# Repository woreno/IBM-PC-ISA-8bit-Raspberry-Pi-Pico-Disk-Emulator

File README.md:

# ISA-Raspberry-Pi-Pico-Disk-Emulator
A Raspberry Pi Pico **floppy disk and harddisk emulator** for older computers/operating systems that **relies only** on BIOS for disk accesses. Its a ISA-8 bit board. "It can let you use it your physical floppy drives or, floppy images on demand, using a tiny screen and a joystick". As this is a DIY electronics and software project, use this at your own risk.
Also the Raspberry Pi Pico C/PIO code is experimental - it just works fine with O0 (despite i attempted to set critical parts to no optimization, i didnt ran) - so this is an open issue, and i had to fine-tune the screen clocks using DEFINEs. 

**Included** 
  - Kicad ISA-8bit prototype schematic
    - this sketch has wide-traces because i use to transfer PCB designs using photo-paper + iron and etch them with ferric chloride (so this process sometimes fails with thin traces, so i use wider traces)  
  - C and ASM code
  - building scripts (windows only)
  - Amstrad PPC512/640 rear expansion DB37 and DB25 ports diagram 
      - this project was tested with an Amstrad PPC640 hence ribbon cables were used instead of a ISA-8bit edge.
  - Memory addressing and connection simple diagrams

**Project Description**

   This ISA-8bit board implements new INT13h and INT19h BIOS software interrupts handlers for disk access and bootstrapping at 0xC8000. Instead of a having the typical ROM, a Raspberry Pi Pico serves these addresses with its own memory. Theres a mini TFT (ST7735), a Joystick, and a SDCard adapter connected by flat ribbon cables that can be attached to a front-panel. The board supports a FAT16 file system containing directories, floppy disk images, and a raw harddisk image (it must be named "hdd.ima" at the root directory). Using the joystick is possible to enable the harddisk image use, navigate SDCard filesystem, and assign floppy disk images to A: and B: drives at any time; theres also the option to select the physical drive instead of floppy disks. The bootstrap code (int19h) is needed for older computers not supporting booting from hard disks so it will place INT13h passing the drive (0x80) and if the hdd.ima file exists, it will boot just as fine.
   The advantage of replacing INT13h or jumping to the factory INT13h, is that is possible to enable the use of the physical drive or using a floppy disk image on demand. However, only ancients Operating Systems uses INT13h directly, so everything that is Windows-386 enhanced mode and beyond - that uses drivers for talking directly with floppy drives and harddisk via IO ports - doesn't belong to this project. 

**Electronics side**
  * Uses 2 74LS244 for multiplexing the address lines A0:A11 to the Raspberry Pi Pico
  * Uses 1 74HC244 for multiplexing the SDCard and TFT lines. The code calls turn_SD() and turnDisplay()
    to activate these lines before placing calls
  * Uses 1 GAL Atmel ATF16v8B for decoding the address 0xC8000 using the A15:A19 lines, along the
    memory read and memory write signals (/MEMR, /MEMW)
  * It pulls down the signal IOREADY using a 2N3904 transistor so it can finish the memory access requests
  * Uses a 2-axis joystick which swings 2 lines between -5V to 5V according to the side (left/right, up/down); these
    lines are connected to 2 ADC channels on the Raspberry Pi Pico
  * Uses 1 74HCT04 for inverting ENABLE_SD and /ENABLE_LOW_ADDR signals for multiplexing some lines, using the 244 buffers
  * Uses some voltage dividers with resistors for 5V to 3.3V level conversion next to some Raspberry Pi Pico GPIO 
  * Uses a bidirectional bus converter TXS0108E, from/to 3.3V to 5V, for the databus interface, operated with a Output Enable Signal to block them from the main 8086 PC databus

**Software side - Raspberry Pi Pico - Core 0**
  * This CPU core is on loop waiting for data from one master PIO program (master_pio). This master_pio is waiting for memr_pio or memw_pio PIO programs for producing and IRQ0.  
  * These previous 2 PIO programs (they are equal, just differ on the line they use, MEMR or MEMW): the PIO program keeps waiting for these signals to be HIGH - they come HIGH from the ATF16v8b when the 0xC8XXX is on the address bus as well one of /MEMR or /MEMW are LOW; after, the PIO Program immediately puts the IOWAIT line to HIGH, and a transistor connected to it, will pull down the IOREADY line to indicate the 8086 that needs more time. After, the master PIO program transfers control to the C program which reads all the address lines (enabling and disabling /EN_ADDR_LOW); reads which MEMR/W line is HIGH accordantly reads or writes the local C-Array, as well controling the databus converter signal DB_ENABLE_OE. At the end, the IOWAIT is lowered, and in case of a writing, the databus is left active for more a period for settling.
  
**Software side - Raspberry Pi Pico - Core 1**
* This CPU core is always on a loop:
    1) pooling the shared area variable "START_OPERATION" flag
    2) pooling the joystick values
    3) updating the graphical interface in the TFT in case of joystick movement
* The INT13h code saves the registers to the shared-variable area, and writes the START_OPERATION flag, as soon this happen the code knowns how to handle INT13h by reading or writing the SDCard. The code extracts the Cylinder-Head-Sector from the CPU registers, converts to LBA and reads and writes accordantly the virtual disk images. The core code and INT13h code uses the shared-buffer for transfering the r/w data; the 8086 CPU or the Raspberry Core is put to rest before the shared-buffer is going to be wrote by one of them.

**Software side - Raspberry Pi Pico - Core 1 - FileSystem and SDCard**
  * The FAT file system access is done with my own  library. Once a floppy disk image is loaded by using the user interface (or hdd.ima is present) the file is checked for contiguityusing "fs_checkSequence" (that's it if the file clusters are sequential, this is basically true when files don't expand) - if is this is true, then the r/w disk access is done faster using "fs_rw_sequential_512B", as the contents are indexed as 512 bytes starting at the first cluster of the file.
  * The SDCard access is done with my own library - it reads/writes 512blocks - incomplete code alert: OLDER SD CARDS might not work. 

**Software side - Raspberry Pi Pico - Core 1 - User interface**
  * The ST7735 TFT screen library its my own. The initialization code was borrowed from https://github.com/afiskon/stm32-st7735/ . This screen seems to demand a RESET line, i don't use it and i connect both RESET and BACKLIGHT lines to a pullup. I found if the initialization code is sent at lower speed, later commands can run at faster speed without requiring a RESET signal several toogling at the initialization. This saved me a 1 GPIO.
  * My own draw library abstracts calls to the screen primitive functions (drawing pixels, rectangles) with preprocessor DEFINEs.
  * My own user-interface library have base and derived classes to create lists with options, also specifing a source class. These later are like adapter classes that enable to create lists from a source, like a text file or a filesystem, in example to render a menu to navigate the master-boot-records and filesystems within. 

**Software side - 8086 PC Option ROM aspects**
  * The 8086-PC BIOS scans the upper memory addresses for option ROMs. These ROMs must include at their first bytes 0xAA55 (2 bytes), the total in 512-bytes blocks(1 byte), and all their bytes shall sum to zero (8-bit sum).
  
**Software side - 8086 PC Option ROM**
  * The ROM in written in ASM and compiled in Turbo Assembler in a DOSBOX enviroment.
  * After the 8086 code is compiled and linked with TASM, a utility strips the MZ-header, sums all bytes and writes the remain to 0, and places this remain into the compiled code, in a reserved, 1-byte place. After, the utility resizes this image to accomodate the buffer, and shared-variables area, and converts it to a C hexadecimal array. This array is included into Raspberry Pi Pico C++ program and has some C identifiers pointing to it. This array is served as the beggining of 0xC8000: boot code, INT13h, INT19h handlers, a buffer reserved for transfering data used by INT13h, a shared-variables-area, and the DBTs (disk base table). The DBTs are BIOS structures are served when INT13h, function 8 (get params) and need to be dinamically changed accordantly the floppy disk image selected (ie, 720KB or 1440KB).
  * When the ROM boots it saves the factory Int13h pointer (sitting at address 4*0x13) into the shared-variables area above the far-jump opcode (0xEA); then replaces the factory pointer at that address with the new Int13h pointer located at 0xC8xxx.
  * On Int19h, the new handler code iterates the 3 drives (0,1,0x80) reading the first sector with Int13h to 0x7C00, checking for the boot flag 0xAA55 at bytes 510 and 511, if success, it jumps to 0x7C00.
  *  On  Int13h, the new handler code will save the registers to the shared-variables area also checking there, if the drive is selected as physical. If physical, it will restore the registers and jump to the far-jump opcode along the saved factory Int13h address (transfering control to the factory Int13h to handle the physical drive). Otherwise the new code it will set the flag START_OPERATION at the shared-variables area to start exchanging data with the Raspberry core, also both using CMD and CMDRES flags to put any of the cpus resting while the other is writting data on the shared-buffer. At the end, the registers likely changed by the C code (for instance for function 8 get params) are restored.

**Software side - ATF16v8b pins logical functions**
  * This code specifies as outputs the MEMR and MEMW pins, these two outputs go to the Raspbery Pi Pico; as inputs the A15:19 address bus lines, /MEMR, /MEMW bus signals. When the A15:19 is 11001, and /MEMR=0 or /MEMW=0 it activates as HIGH the MEMR or MEMW output pins, thus decoding the 0xC8XXX address on memory accesses.

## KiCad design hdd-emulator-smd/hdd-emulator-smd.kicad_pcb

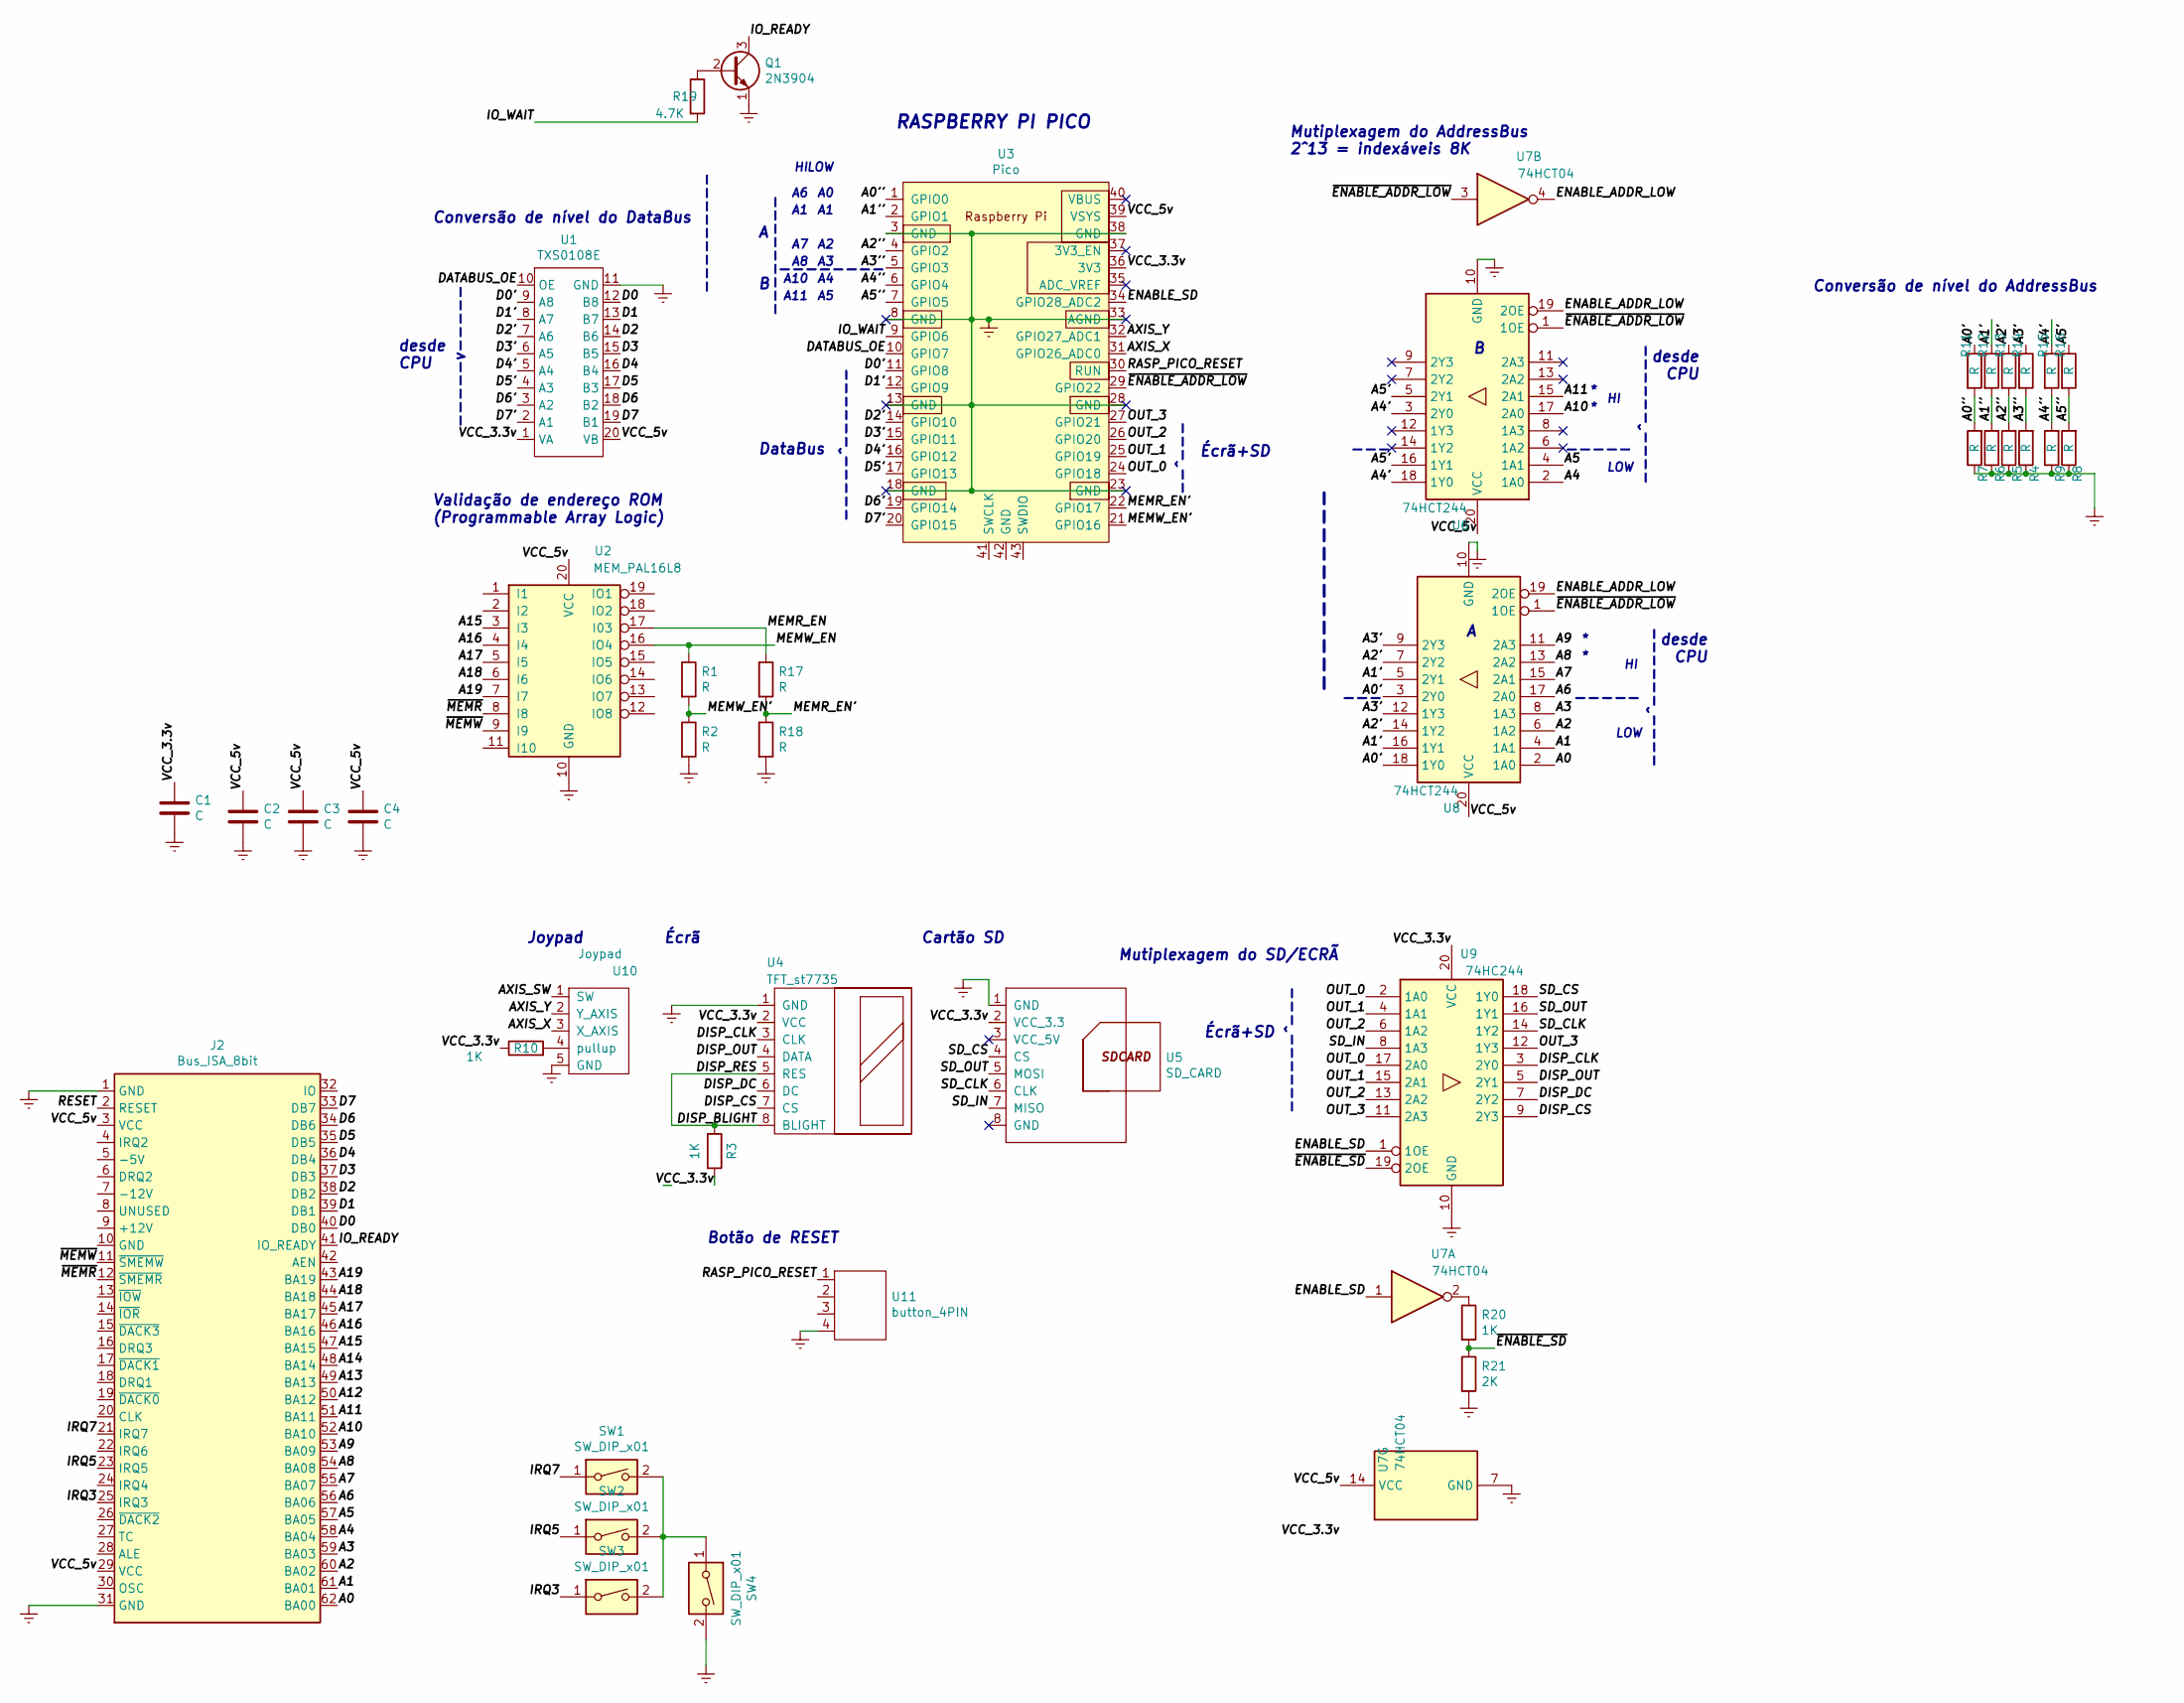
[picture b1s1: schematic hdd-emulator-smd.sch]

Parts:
C1, C2, C3, C4: C; standard_2pins_half
J2: Bus_ISA_8bit; ISA_8bit_edge
Q1: 2N3904; TO-92_Inline
R1, R2, R4, R5, R6, R7, R8, R9, R11, R12, R13, R14, R15, R16, R17, R18: R; R_0201_0603Metric
R3, R10, R20: 1K; R_0201_0603Metric
R19: 4.7K; R_0201_0603Metric
R21: 2K; R_0201_0603Metric
SW1, SW2, SW3, SW4: SW_DIP_x01; jumper_set_1
U1: TXS0108E; standard_DIP_10pins_doubleBody
U2: MEM_PAL16L8; standard_DIP_20pins_thin_body
U3: Pico; RPi_Pico_SMD_THT
U4: TFT_st7735; PinHeader_1x08_P2.54mm_Vertical
U5: SD_CARD; PinHeader_1x08_P2.54mm_Vertical
U6, U8: 74HCT244; standard_DIP_20pins_thin_body
U7: 74HCT04; standard_DIP_14OvalPins
U9: 74HC244; standard_DIP_20pins_thin_body
U10: Joypad; PinHeader_1x05_P2.54mm_Vertical
U11: button_4PIN; BUTTON_4PIN

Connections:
/A0: J2.62 (BA00), U8.2 (1A0)
/A0': R11.1, U8.3 (2Y0), U8.18 (1Y0)
/A0'': R7.2, R11.2, U3.1 (GPIO0)
/A1: J2.61 (BA01), U8.4 (1A1)
/A1': R12.1, U8.5 (2Y1), U8.16 (1Y1)
/A1'': R6.2, R12.2, U3.2 (GPIO1)
/A2: J2.60 (BA02), U8.6 (1A2)
/A2': R13.1, U8.7 (2Y2), U8.14 (1Y2)
/A2'': R5.2, R13.2, U3.4 (GPIO2)
/A3: J2.59 (BA03), U8.8 (1A3)
/A3': R14.1, U8.9 (2Y3), U8.12 (1Y3)
/A3'': R4.2, R14.2, U3.5 (GPIO3)
/A4: J2.58 (BA04), U6.2 (1A0)
/A4': R15.1, U6.3 (2Y0), U6.18 (1Y0)
/A4'': R9.2, R15.2, U3.6 (GPIO4)
/A5: J2.57 (BA05), U6.4 (1A1)
/A5': R16.1, U6.5 (2Y1), U6.16 (1Y1)
/A5'': R8.2, R16.2, U3.7 (GPIO5)
/A6: J2.56 (BA06), U8.17 (2A0)
/A7: J2.55 (BA07), U8.15 (2A1)
/A8: J2.54 (BA08), U8.13 (2A2)
/A9: J2.53 (BA09), U8.11 (2A3)
/A10: J2.52 (BA10), U6.17 (2A0)
/A11: J2.51 (BA11), U6.15 (2A1)
/A12: J2.50 (BA12)
/A13: J2.49 (BA13)
/A14: J2.48 (BA14)
/A15: J2.47 (BA15), U2.3 (I3)
/A16: J2.46 (BA16), U2.4 (I4)
/A17: J2.45 (BA17), U2.5 (I5)
/A18: J2.44 (BA18), U2.6 (I6)
/A19: J2.43 (BA19), U2.7 (I7)
/AXIS_SW: U10.1 (SW)
/AXIS_X: U3.31 (GPIO26_ADC0), U10.3 (X_AXIS)
/AXIS_Y: U3.32 (GPIO27_ADC1), U10.2 (Y_AXIS)
/D0: J2.40 (DB0), U1.12 (B8)
/D0': U1.9 (A8), U3.11 (GPIO8)
/D1: J2.39 (DB1), U1.13 (B7)
/D1': U1.8 (A7), U3.12 (GPIO9)
/D2: J2.38 (DB2), U1.14 (B6)
/D2': U1.7 (A6), U3.14 (GPIO10)
/D3: J2.37 (DB3), U1.15 (B5)
/D3': U1.6 (A5), U3.15 (GPIO11)
/D4: J2.36 (DB4), U1.16 (B4)
/D4': U1.5 (A4), U3.16 (GPIO12)
/D5: J2.35 (DB5), U1.17 (B3)
/D5': U1.4 (A3), U3.17 (GPIO13)
/D6: J2.34 (DB6), U1.18 (B2)
/D6': U1.3 (A2), U3.19 (GPIO14)
/D7: J2.33 (DB7), U1.19 (B1)
/D7': U1.2 (A1), U3.20 (GPIO15)
/DATABUS_OE: U1.10 (OE), U3.10 (GPIO7)
/DISP_BLIGHT: R3.1, U4.5 (RES), U4.8 (BLIGHT)
/DISP_CLK: U4.3 (CLK), U9.3 (2Y0)
/DISP_CS: U4.7 (CS), U9.9 (2Y3)
/DISP_DC: U4.6 (DC), U9.7 (2Y2)
/DISP_OUT: U4.4 (DATA), U9.5 (2Y1)
/ENABLE_ADDR_LOW: U6.19 (2OE), U7.4, U8.19 (2OE)
/ENABLE_SD: U3.34 (GPIO28_ADC2), U7.1, U9.1 (1OE)
/IO_READY: J2.41 (IO_READY), Q1.3 (C)
/IO_WAIT: R19.2, U3.9 (GPIO6)
/IRQ3: J2.25 (IRQ3), SW3.1
/IRQ5: J2.23 (IRQ5), SW2.1
/IRQ7: J2.21 (IRQ7), SW1.1
/MEMR_EN: R17.1, U2.17 (I03)
/MEMR_EN': R17.2, R18.1, U3.22 (GPIO17)
/MEMW_EN: R1.1, U2.16 (IO4)
/MEMW_EN': R1.2, R2.1, U3.21 (GPIO16)
/OUT_0: U3.24 (GPIO18), U9.2 (1A0), U9.17 (2A0)
/OUT_1: U3.25 (GPIO19), U9.4 (1A1), U9.15 (2A1)
/OUT_2: U3.26 (GPIO20), U9.6 (1A2), U9.13 (2A2)
/OUT_3: U3.27 (GPIO21), U9.11 (2A3), U9.12 (1Y3)
/RASP_PICO_RESET: U3.30 (RUN), U11.1
/RESET: J2.2 (RESET)
/SD_CLK: U5.6 (CLK), U9.14 (1Y2)
/SD_CS: U5.4 (CS), U9.18 (1Y0)
/SD_IN: U5.7 (MISO), U9.8 (1A3)
/SD_OUT: U5.5 (MOSI), U9.16 (1Y1)
/VCC_3.3v: C1.1, R3.2, R10.1, U1.1 (VA), U3.36 (3V3), U4.2 (VCC), U5.2 (VCC_3.3), U9.20 (VCC)
/VCC_5v: C2.1, C3.1, C4.1, J2.3 (VCC), J2.29 (VCC), U1.20 (VB), U2.20 (VCC), U3.39 (VSYS), U6.20 (VCC), U7.14 (VCC), U8.20 (VCC)
/~ENABLE_ADDR_LOW: U3.29 (GPIO22), U6.1 (1OE), U7.3, U8.1 (1OE)
/~ENABLE_SD: R20.2, R21.1, U9.19 (2OE)
/~MEMR: J2.12 (~SMEMR), U2.8 (I8)
/~MEMW: J2.11 (~SMEMW), U2.9 (I9)
GNDREF: C1.2, C2.2, C3.2, C4.2, J2.1 (GND), J2.31 (GND), Q1.1 (E), R2.2, R4.1, R5.1, R6.1, R7.1, R8.1, R9.1, R18.2, R21.2, SW4.2, U1.11 (GND), U2.10 (GND), U3.3 (GND), U3.8 (GND), U3.13 (GND), U3.18 (GND), U3.23 (GND), U3.28 (GND), U3.33 (AGND), U3.38 (GND), U4.1 (GND), U5.1 (GND), U6.10 (GND), U7.7 (GND), U8.10 (GND), U9.10 (GND), U10.5 (GND), U11.4
unnamed: Q1.2 (B), R19.1
unnamed: R10.2, U10.4 (pullup)
unnamed: R20.1, U7.2
unnamed: SW1.2, SW2.2, SW3.2, SW4.1

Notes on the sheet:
Conversão de nível do DataBus
Écrã+SD
--^---
Conversão de nível do AddressBus
-----^------
DataBus
Mutiplexagem do SD/ECRÃ
-----v-----
Écrã
Cartão SD
desde CPU
----^------
---
-----
Botão de RESET
Joypad
------^---
--------
A10
A11
LOW
---------
-----------
2^13 = indexáveis 8K
Mutiplexagem do AddressBus
RASPBERRY PI PICO
Validação de endereço ROM (Programmable Array Logic)

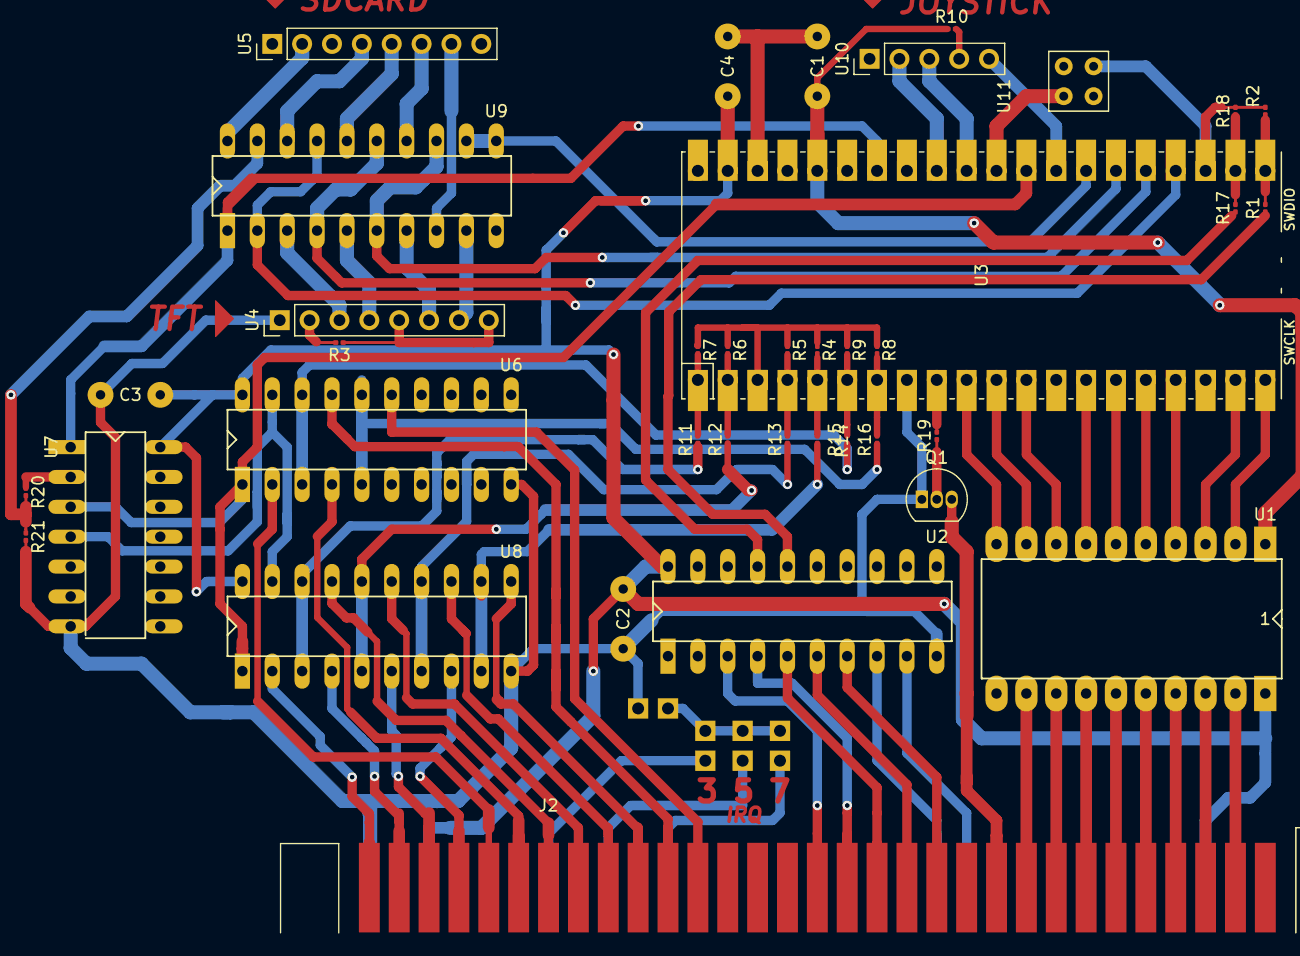
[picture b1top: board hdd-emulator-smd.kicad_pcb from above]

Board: 2 copper layers, 42 parts (0 on the bottom side), 84 nets.

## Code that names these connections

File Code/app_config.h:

// DEBUG DE PINOS --------------------------------------------


//#define FS_USES_EXTERNAL_BUFFER		mcuSharedBuffer
#define FS_FSNODE_HAS_PRINT

#define DEBUG_USB(STR_,...) 
#define mcu_log(STR_,...) 	

#define APP_DEBUG
#define DEBUG(X,...) printf(X, __VA_ARGS__);

// Definiçoes ------------------------------------------------

#define APP_START_DELAY			500 // tempo para poder abrir o putty
#define DELAY_SHORT_			asm volatile("nop \n nop \n nop \n nop \n nop \n nop \n nop \n nop \n nop");
#define DELAY_SHORT				DELAY_SHORT_ DELAY_SHORT_ DELAY_SHORT_ DELAY_SHORT_ DELAY_SHORT_  
 
////////////////////////////////////////////////////////////////////////////////
// ADDRESS BUS
////////////////////////////////////////////////////////////////////////////////

	#define PIN_MEM_WRITE		IO_PIN_5    // pino 7
	#define PIN_MEM_READ		IO_PIN_6	// pino 9

	#define PIN_ADDR_MUX		IO_PIN_22	//ativo a LOW
	#define PIN_ENABLE_DB_OUT	IO_PIN_15	//ativo a HI

	#define PIN_A0				IO_PIN_16
	#define PIN_A1				IO_PIN_17
	#define PIN_A2				IO_PIN_18
	#define PIN_A3				IO_PIN_19
	#define PIN_A4				IO_PIN_20
	#define PIN_A5				IO_PIN_21

	#define PIN_A6				IO_PIN_16
	#define PIN_A7				IO_PIN_17
	#define PIN_A8				IO_PIN_18
	#define PIN_A9				IO_PIN_19
	#define PIN_A10				IO_PIN_20
	#define PIN_A11				IO_PIN_21

	// *5
			

////////////////////////////////////////////////////////////////////////////////
// DATABUS
////////////////////////////////////////////////////////////////////////////////

	#define PIN_D0			IO_PIN_7
	#define PIN_D1			IO_PIN_8
	#define PIN_D2			IO_PIN_9
	#define PIN_D3			IO_PIN_10
	#define PIN_D4			IO_PIN_11
	#define PIN_D5			IO_PIN_12
	#define PIN_D6			IO_PIN_13
	#define PIN_D7			IO_PIN_14

#define DB_PINS_DEF(X_)\
	X_(PIN_D0,			 "p0")\
	X_(PIN_D1,			 "p1")\
	X_(PIN_D2,			 "p2")\
	X_(PIN_D3,			 "p3")\
	X_(PIN_D4,			 "p4")\
	X_(PIN_D5,			 "p5")\
	X_(PIN_D6,			 "p6")\
	X_(PIN_D7,			 "p7")

	//    ... .... . <- inicio databus
	// 6 5432 1098 7654 3210	posicao
	// 0 0111 1111 1000 0000	binario
	//     7    F   8	0		hexadecimal

	#define DATABUS_PIN_MASK		0x7F80
 
	#define DATABUS_OE_ON			PIN_WRITE(PIN_ENABLE_DB_OUT, 1);
	#define DATABUS_OE_OFF			PIN_WRITE(PIN_ENABLE_DB_OUT, 0);

////////////////////////////////////////////////////////////////////////////////
// JOYPAD
////////////////////////////////////////////////////////////////////////////////

	#define PIN_MEM_WAIT			IO_PIN_ADC1
	#define PIN_SMALL_JOYSTICK_Y	IO_PIN_ADC0
	#define PIN_SMALL_JOYSTICK_X	IO_PIN_ADC2

////////////////////////////////////////////////////////////////////////////////
// AUDIO
////////////////////////////////////////////////////////////////////////////////

//	#define AUDIOPLAYER_PIN_GENERIC_BUTTON		PIN_BUTTON_RIGHT
//	#define PIN_BUZZER							IO_PIN_1
//	#define PIN_MIC_IN_LEFT						IO_PIN_ADC2
//	#define PIN_MIC_IN_RIGHT					IO_PIN_ADC1 
//	#define PIN_ULTRASPEAKER					IO_PIN_ADC0


////////////////////////////////////////////////////////////////////////////////
// DISCO SD
////////////////////////////////////////////////////////////////////////////////
	
	#define APP_USES_SD
	#define SD_USES_FAST_CLOCK
	#define SD_ENABLE_DATA_CRC		0
	#define PIN_SD_CS				IO_PIN_0
	#define PIN_SD_OUT				IO_PIN_1
	#define PIN_SD_CLK				IO_PIN_2
	#define PIN_SD_IN				IO_PIN_3 //IO_PIN_5
	#define PIN_DISP_ENABLE			IO_PIN_4

	#include "sd.h"

// no adaptador...
	#define SD_PINS_DEF(X_)\
		X_(PIN_SD_CS,				"p0")\
		X_(PIN_SD_OUT,				"p1")\
		X_(PIN_SD_CLK,				"p2")

////////////////////////////////////////////////////////////////////////////////
// ECRÃ
////////////////////////////////////////////////////////////////////////////////

	#define PIN_DISP_CLK			IO_PIN_0
	#define PIN_DISP_OUT			IO_PIN_1
	#define PIN_DISP_DC				IO_PIN_2
	#define PIN_DISP_CS				IO_PIN_3
	//#define PIN_DISP_RES			IO_PIN_13
	//#define PIN_DISP_BRIGHT		IO_PIN_ADC2

	#define APP_USES_ICONS
	#define DRAW_USES_BUFFER
	#include "st7735.h"
	#include "uiIcons.h"
	#include "draw.h"

#define DISP_PINS_DEF(X_)\
	X_(PIN_DISP_CLK,			 "p0")\
	X_(PIN_DISP_OUT,			 "p1")\
	X_(PIN_DISP_DC,				 "p2")\
	X_(PIN_DISP_CS,				 "p3")


////////////////////////////////////////////////////////////////////////////////
// FS 
////////////////////////////////////////////////////////////////////////////////

	#define FS_FAT_USE_CACHE_WITH_SIZE	512
	#define DEV_RD_BLOCK				sd_rd_block
	#define DEV_WR_BLOCK				sd_wr_block
	#include "fs.h"

////////////////////////////////////////////////////////////////////////////////
// BUZZER 
////////////////////////////////////////////////////////////////////////////////

	#define PIN_BUZZER 99
	#include "sound.h"

////////////////////////////////////////////////////////////////////////////////
// UI 
//////////////////////////////////////////////////////////////////////////////// 
	#define UI_CACHEFILES_MAXSIZE	12		

	#define UI_ANIMATE_SELECTION    0
	#define UI_ANIMATE_DIR          0//40
	#define UI_ANIMATE_DIR_BUFF		1		// se 1 usa um buffer para animacao (+20K)
	#define UI_MENU_TEXT_RBORDER_DX 4
	#define UI_MENU_OPTION_DY		20
	#define UI_MENU_TITLE_DY		20
	#define UI_MENU_TITLE_PENX		2
	#define UI_MENU_TITLE_PENY		(fontBlockY-1)
	#define UI_MENU_TEXT_PENX		22
	#define UI_MENU_TEXT_PENY		(fontBlockY-1)
	#define UI_MENU_ICON_PENX		3
	#define UI_MENU_ICON_PENY		2

	W0 ui_uninstall_buttons(){}
	#include "uiHeads.h"
	 

#if (defined(DEBUG_PINS_SD) || defined(DEBUG_PINS_DISP) || defined(DEBUG_PINS_AUDIO) || defined(DEBUG_PINS_PERIPHERAL))
	#define   DEBUG_PINS
#endif

 



W0  init_pins()
{
	
	PIN_INIT(PIN_MEM_WAIT)
	PIN_MODE(PIN_MEM_WAIT, PIN_MODE_OUTPUT)
	PIN_WRITE(PIN_MEM_WAIT, 0);

	// NÃO CONDUZIR O DATABUS ALTA IMPEDANCIA
	// o DATABUS está direto ao CPU com um conversor de nivel
	PIN_INIT(PIN_ENABLE_DB_OUT)
	PIN_MODE(PIN_ENABLE_DB_OUT, PIN_MODE_OUTPUT)
	DATABUS_OE_OFF			// OE = 0 ALTA IMPEDANCIA
	
	// CS
	DATABUS_OE_ON			// OE = 1

	PIN_INIT(PIN_LED)
	PIN_MODE(PIN_LED,			PIN_MODE_OUTPUT)
	
	PIN_INIT(PIN_DISP_ENABLE)
	PIN_MODE(PIN_DISP_ENABLE,		PIN_MODE_OUTPUT)
	
	PIN_INIT(PIN_DISP_ENABLE)
	PIN_MODE(PIN_DISP_ENABLE,		PIN_MODE_OUTPUT)
	
	PIN_INIT(PIN_SMALL_JOYSTICK_Y)
	PIN_INIT(PIN_SMALL_JOYSTICK_X)
    adc_gpio_init(PIN_SMALL_JOYSTICK_X);
    adc_gpio_init(PIN_SMALL_JOYSTICK_Y);
	adc_init();
	
	PIN_MODE(PIN_SMALL_JOYSTICK_X,   PIN_MODE_INPUT)
	PIN_MODE(PIN_SMALL_JOYSTICK_Y,   PIN_MODE_INPUT)
} 
W0 turnSD()
{
	if (dispMux == DISPSD_MUX_SD_IS_ON) return;
	dispMux = DISPSD_MUX_SD_IS_ON;
	PIN_MODE(PIN_SD_IN, PIN_MODE_INPUT);
	PIN_WRITE(PIN_DISP_ENABLE,  0); 
	DELAY_MS(2);
	sd_init();
	DELAY_MS(2);
}
W0 turnDisplay()
{
	if (dispMux== DISPSD_MUX_DISP_IS_ON) return;
	dispMux = DISPSD_MUX_DISP_IS_ON;
	PIN_MODE(PIN_DISP_CS, PIN_MODE_OUTPUT);
	PIN_WRITE(PIN_DISP_ENABLE,  1); DELAY_MS(2);
}


//#define APP_DEBUG_MEMORY_ACCESS
volatile W32 trapNumberFRD=0;
volatile W32 trapNumberFWR=0;
volatile W32 trapNumberR=0;
volatile W32 trapNumberW=0;
volatile W32 trapNumberBRD=0;
volatile W32 trapNumberBWR=0;
volatile W32 forbiddenWrites=0;
//volatile W32 forbiddenWritesAddr[128];
#ifdef APP_DEBUG_MEMORY_ACCESS
	W32 trapsAddressesR[512];
	W32 trapsAddressesW[512];
#endif
